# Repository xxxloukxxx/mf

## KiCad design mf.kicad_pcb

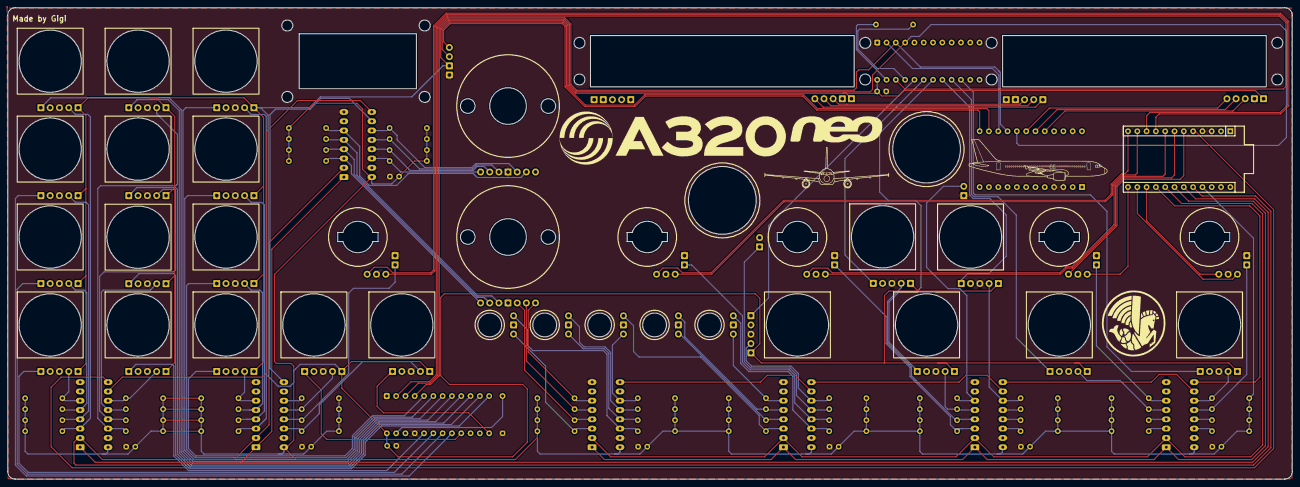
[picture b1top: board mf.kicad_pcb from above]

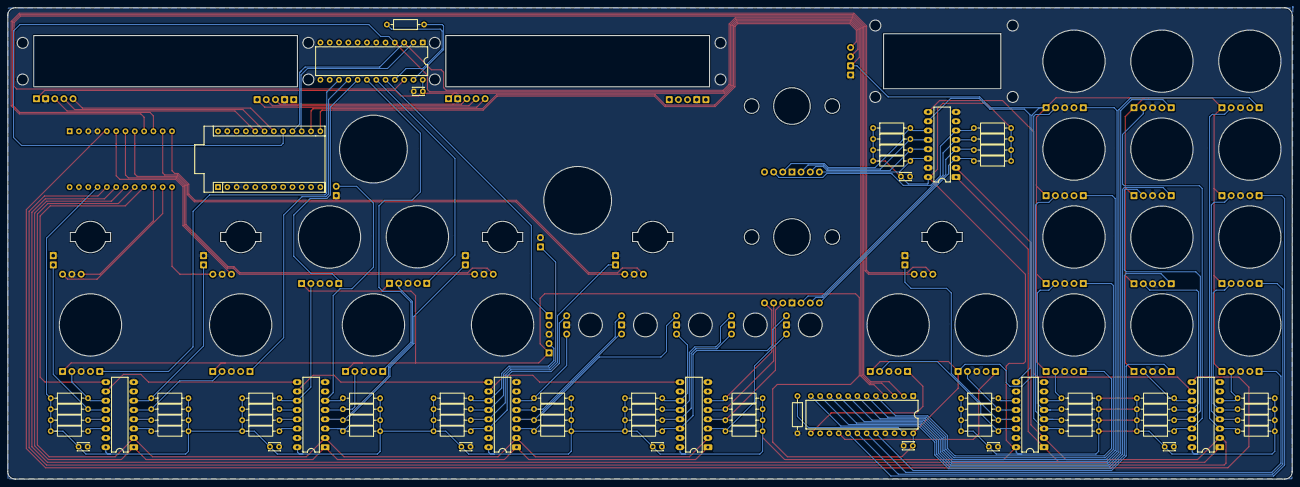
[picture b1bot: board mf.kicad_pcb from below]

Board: 2 copper layers, 350.6 x 128.7 mm, 115 parts (77 on the bottom side), 115 nets.

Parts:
BC1, BC2, BC3, BC4, BC5, BC6, BC7, BC8, BC9, BC10, BC11, BC12, BC13, BC14, BC15, BC16, BC17, BC18, BC19, BC20: sq_but
C1, C2, C3, C5, C6, C7, C8, C9, C10: Capacitor_NP; C_Disc_D3.0mm_W2.0mm_P2.50mm
E1, E2, E3, E4, E5: ec11-ext
R1, R2, R3, R4, R5, R6, R7, R8, R9, R10, R11, R12, R13, R14, R15, R16, R17, R18, R19, R20, R21, R22, R23, R24, R34, R35, R36, R38, R39, R40, R41, R42, R43, R44, R45, R46, R47, R48, R49, R50, R51, R52, R53, R54, R55, R56, R57, R58, R59, R60, R61, R62, R63, R64, R65, R66: Resistor; R_Axial_DIN0207_L6.3mm_D2.5mm_P10.16mm_Horizontal
R33, R37: R; R_Axial_DIN0207_L6.3mm_D2.5mm_P10.16mm_Horizontal
RB4, RB5: r_but
U1, U7: Sparkfun_Pro_Micro
U2, U4: 7seg_x8
U3: 7seg_x4
U5, U6, U8, U14, U16, U17, U19: 74HC165; DIP-16_W7.62mm_LongPads
U9, U11: DM13a; DIP-24_W10.16mm
U12, U13: 5_6-pos-switch
U15, U18, U20, U21, U22: 3posswitch

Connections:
+5V: C1.2, C2.2, C3.2, C5.2, C6.2, C7.2, C8.2, R1.1, R2.1, R3.1, R4.1, R5.1, R6.1, R7.1, R8.1, R9.1, R10.1, R11.1, R12.1, R13.1, R14.1, R15.1, R16.1, R17.1, R18.1, R19.1, R20.1, R21.1, R22.1, R23.1, R24.1, R34.1, R35.1, R36.1, R38.1, R39.1, R40.1, R41.1, R42.1, R43.1, R44.1, R45.1, R46.1, R47.1, R48.1, R49.1, R50.1, R51.1, R52.1, R53.1, R54.1, R55.1, R56.1, R57.1, R58.1, R59.2, R60.2, R61.2, R62.2, R63.1, R64.1, R65.1, R66.1, U1.21 (VCC), U5.16 (VCC), U6.16 (VCC), U8.16 (VCC), U14.16 (VCC), U16.16 (VCC), U17.16 (VCC), U19.16 (VCC)
+5VPW: BC1.5 (GND), BC2.5 (GND), BC3.5 (GND), BC4.5 (GND), BC5.5 (GND), BC6.5 (GND), BC7.5 (GND), BC8.5 (GND), BC9.5 (GND), BC10.5 (GND), BC11.5 (GND), BC12.5 (GND), BC13.5 (GND), BC14.5 (GND), BC15.5 (GND), BC16.5 (GND), BC17.5 (GND), BC18.5 (GND), BC19.5 (GND), BC20.5 (GND), C9.2, C10.2, U2.1 (5V), U3.3 (5V), U4.1 (5V), U9.24 (VCC), U11.24 (VCC)
/Input/E1_A: E1.1 (A), U1.15 (D14)
/Input/E1_B: E1.3 (B), U1.14 (D16)
/Input/E2_A: E2.1 (A), U1.6 (~D3)
/Input/E2_B: E2.3 (B), U1.13 (~D10/A10)
/Input/E3_A: E3.1 (A), U1.8 (~D5)
/Input/E3_B: E3.3 (B), U1.7 (D4/A6)
/Input/E4_A: E4.1 (A), U1.12 (~D9/A9)
/Input/E4_B: E4.3 (B), U1.11 (D8/A8)
/Input/E5_A: E5.1 (A), U1.9 (~D6/A7)
/Input/E5_B: E5.3 (B), U1.10 (D7)
/Input/I_CLK_L: U1.18 (D19/A1), U5.1 (~PL), U6.1 (~PL), U8.1 (~PL), U14.1 (~PL)
/Input/I_CLK_R: U1.20 (D21/A3), U16.2 (CP), U17.2 (CP), U19.2 (CP)
/Input/I_DATA_L: U1.16 (D15), U5.9 (Q7)
/Input/I_DATA_R: U1.5 (D2), U19.9 (Q7)
/Input/I_LATCH_L: U1.17 (D18/A0), U5.2 (CP), U6.2 (CP), U8.2 (CP), U14.2 (CP)
/Input/I_LATCH_R: U1.19 (D20/A2), U16.1 (~PL), U17.1 (~PL), U19.1 (~PL)
/Input/LED_BC1: BC1.4 (LED), U11.15 (OUT10)
/Input/LED_BC2: BC2.4 (LED), U11.16 (OUT11)
/Input/LED_BC3: BC3.4 (LED), U11.17 (OUT12)
/Input/LED_BC4: BC4.4 (LED), U11.18 (OUT13)
/Input/LED_BC5: BC5.4 (LED), U11.19 (OUT14)
/Input/LED_BC6: BC6.4 (LED), U11.20 (OUT15)
/Input/LED_BC7: BC7.4 (LED), U9.13 (OUT8)
/Input/LED_BC8: BC8.4 (LED), U9.16 (OUT11)
/Input/LED_BC9: BC9.4 (LED), U9.5 (OUT0)
/Input/LED_BC10: BC10.4 (LED), U9.20 (OUT15)
/Input/LED_BC11: BC11.4 (LED), U9.19 (OUT14)
/Input/LED_BC12: BC12.4 (LED), U9.6 (OUT1)
/Input/LED_BC13: BC13.4 (LED), U9.12 (OUT7)
/Input/LED_BC14: BC14.4 (LED), U9.18 (OUT13)
/Input/LED_BC15: BC15.4 (LED), U9.7 (OUT2)
/Input/LED_BC16: BC16.4 (LED), U9.11 (OUT6)
/Input/LED_BC17: BC17.4 (LED), U9.17 (OUT12)
/Input/LED_BC18: BC18.4 (LED), U9.8 (OUT3)
/Input/LED_BC19: BC19.4 (LED), U9.10 (OUT5)
/Input/LED_BC20: BC20.4 (LED), U9.9 (OUT4)
/Output/O_4_CLK: U3.1 (CLK), U7.13 (~D10/A10)
/Output/O_4_DIN: U3.2 (DIN), U7.14 (D16)
/Output/O_8_CLK: U4.5 (CLK), U7.18 (D19/A1)
/Output/O_8_CS: U4.4 (CS), U7.19 (D20/A2)
/Output/O_8_DIN: U4.3 (DIN), U7.20 (D21/A3)
/Output/O_CLK: U7.16 (D15), U9.3 (DCK), U11.3 (DCK)
/Output/O_DATA: U7.15 (D14), U11.2 (DAI)
/Output/O_LATCH: U7.17 (D18/A0), U9.4 (LAT), U11.4 (LAT)
GND: BC1.2 (C), BC2.2 (C), BC3.2 (C), BC4.2 (C), BC5.2 (C), BC6.2 (C), BC7.2 (C), BC8.2 (C), BC9.2 (C), BC10.2 (C), BC11.2 (C), BC12.2 (C), BC13.2 (C), BC14.2 (C), BC15.2 (C), BC16.2 (C), BC17.2 (C), BC18.2 (C), BC19.2 (C), BC20.2 (C), C1.1, C2.1, C3.1, C5.1, C6.1, C7.1, C8.1, C9.1, C10.1, E1.2 (COM), E1.5 (E), E2.2 (COM), E2.5 (E), E3.2 (COM), E3.5 (E), E4.2 (COM), E4.5 (E), E5.2 (COM), E5.5 (E), R37.2, RB4.1, RB5.2, U1.3 (GND), U1.4 (GND), U1.23 (GND), U2.2 (GND), U2.7 (GND), U3.4 (GND), U4.2 (GND), U4.7 (GND), U5.8 (GND), U5.15 (~CE), U6.8 (GND), U6.15 (~CE), U7.3 (GND), U7.4 (GND), U7.23 (GND), U8.8 (GND), U8.15 (~CE), U9.1 (GND), U9.21 (ENB), U11.1 (GND), U12.7 (GND), U13.7 (GND), U14.8 (GND), U14.15 (~CE), U15.3 (GND), U16.8 (GND), U16.15 (~CE), U17.8 (GND), U17.15 (~CE), U18.3 (GND), U19.8 (GND), U19.15 (~CE), U20.3 (GND), U21.3 (GND), U22.3 (GND)
unnamed: BC1.3 (NO), R1.2, U5.11 (D0)
unnamed: BC2.3 (NO), R7.2, U5.5 (D6)
unnamed: BC3.3 (NO), R17.2, U8.11 (D0)
unnamed: BC4.3 (NO), R23.2, U8.5 (D6)
unnamed: BC5.3 (NO), R22.2, U8.4 (D5)
unnamed: BC6.3 (NO), R34.2, U14.11 (D0)
unnamed: BC7.3 (NO), R54.2, U17.14 (D3)
unnamed: BC8.3 (NO), R52.2, U17.12 (D1)
unnamed: BC9.3 (NO), R58.2, U17.6 (D7)
unnamed: BC10.3 (NO), R59.1, U19.11 (D0)
unnamed: BC11.3 (NO), R66.2, U19.6 (D7)
unnamed: BC12.3 (NO), R57.2, U17.5 (D6)
unnamed: BC13.3 (NO), R60.1, U19.12 (D1)
unnamed: BC14.3 (NO), R65.2, U19.5 (D6)
unnamed: BC15.3 (NO), R56.2, U17.4 (D5)
unnamed: BC16.3 (NO), R61.1, U19.13 (D2)
unnamed: BC17.3 (NO), R64.2, U19.4 (D5)
unnamed: BC18.3 (NO), R55.2, U17.3 (D4)
unnamed: BC19.3 (NO), R62.1, U19.14 (D3)
unnamed: BC20.3 (NO), R63.2, U19.3 (D4)
unnamed: E1.4 (D), R2.2, U5.12 (D1)
unnamed: E2.4 (D), R8.2, U5.6 (D7)
unnamed: E3.4 (D), R21.2, U8.3 (D4)
unnamed: E4.4 (D), R36.2, U14.13 (D2)
unnamed: E5.4 (D), R53.2, U17.13 (D2)
unnamed: U2.5 (CLK), U4.10 (CLK)
unnamed: U2.4 (CS), U4.9 (LODA)
unnamed: U2.3 (DIN), U4.8 (DOUT)
unnamed: R3.2, U5.13 (D2)
unnamed: R4.2, U5.14 (D3)
unnamed: R5.2, U5.3 (D4)
unnamed: R6.2, U5.4 (D5)
unnamed: U5.10 (DS), U8.9 (Q7)
unnamed: R16.2, U6.11 (D0), U21.1
unnamed: R15.2, U6.12 (D1), U18.2
unnamed: R14.2, U6.13 (D2), U18.1
unnamed: R13.2, U6.14 (D3), U15.2
unnamed: R12.2, U6.3 (D4), U15.1
unnamed: R11.2, U6.4 (D5), U13.4
unnamed: R10.2, U6.5 (D6), U13.5
unnamed: R9.2, U6.6 (D7), U13.6
unnamed: R18.2, U8.12 (D1)
unnamed: R19.2, U8.13 (D2)
unnamed: R20.2, U8.14 (D3)
unnamed: R24.2, RB5.1, U8.6 (D7)
unnamed: R37.1, U9.23 (REXT)
unnamed: U9.2 (DAI), U11.22 (DAO)
unnamed: R33.2, U11.21 (ENB)
unnamed: R33.1, U11.23 (REXT)
unnamed: R35.2, RB4.2, U14.12 (D1)
unnamed: R38.2, U14.14 (D3), U20.2
unnamed: R39.2, U14.3 (D4), U21.2
unnamed: R40.2, U14.4 (D5), U22.1
unnamed: R41.2, U14.5 (D6), U22.2
unnamed: R42.2, U14.6 (D7), U20.1
unnamed: U6.9 (Q7), U14.10 (DS)
unnamed: U8.10 (DS), U14.9 (Q7)
unnamed: R50.2, U12.4, U16.11 (D0)
unnamed: R49.2, U12.3, U16.12 (D1)
unnamed: R48.2, U12.2, U16.13 (D2)
unnamed: R47.2, U12.1, U16.14 (D3)
unnamed: R46.2, U13.1, U16.3 (D4)
unnamed: R45.2, U13.2, U16.4 (D5)
unnamed: R44.2, U13.3, U16.5 (D6)
unnamed: R43.2, U12.5, U16.6 (D7)
unnamed: U16.10 (DS), U17.9 (Q7)
unnamed: U16.9 (Q7), U19.10 (DS)
unnamed: R51.2, U17.11 (D0)

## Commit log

2026-06-01 New schematic
2026-06-02 Update schematic with nearly everything
2026-06-03 New pcb and 3 pos switch footprint
2026-06-14 Begin PCB routing + change in schematic
2026-06-15 Nearly finished just need to add the footprint for the 5/6 pos switch and connect to the rest ! And it will be going into production !
2026-06-20 last footprint and some graphics added
2026-06-22 Final commit (i hope) !
